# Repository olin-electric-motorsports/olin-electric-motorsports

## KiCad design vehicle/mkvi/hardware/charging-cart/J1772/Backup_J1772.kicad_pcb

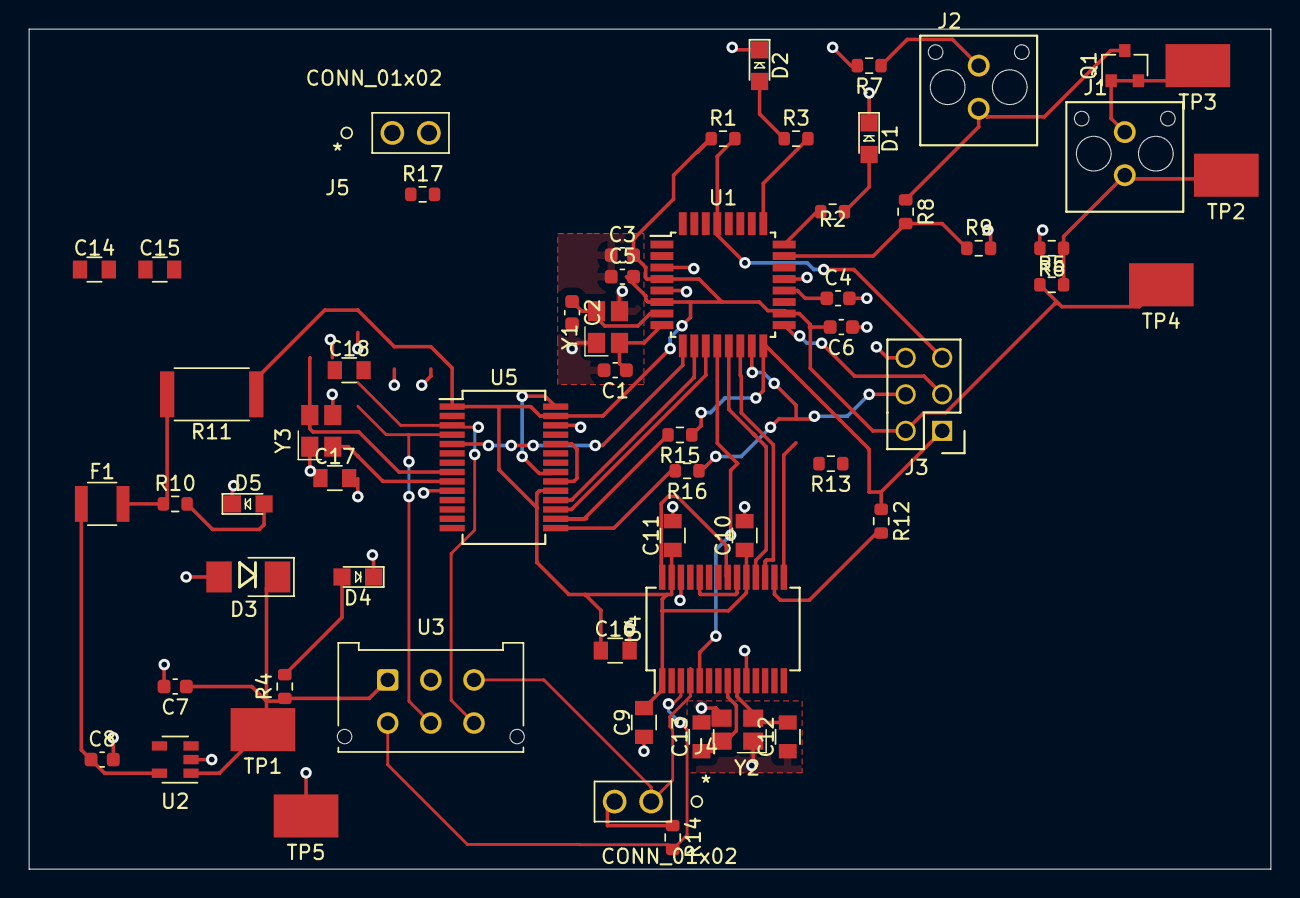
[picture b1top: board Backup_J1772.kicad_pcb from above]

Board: 2 copper layers, 86.4 x 58.4 mm, 60 parts (0 on the bottom side), 47 nets.

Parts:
C1, C2: C_30pF; C_0603_1608Metric
C3, C5, C6: C_0.1uF; C_0603_1608Metric
C4: C_100nF; C_0603_1608Metric
C7, C8: C_1uF; C_0603_1608Metric
C9, C10, C11, C14, C15, C16: C_0.1uF; C_0805_OEM
C12, C13, C17, C18: C_30pF; C_0805_OEM
D1: LED_0805_Red; LED_0805_OEM
D2, D4, D5: LED_0805; LED_0805_OEM
D3: D_Zener_18V; DO-214AA
F1: F_500mA_16V; Fuse_1210
J1, J2: MicroFit_V_2
J3: CONN_02X03; Pin_Header_Straight_2x03
J4, J5: CONN_01x02; pinheader_1x2
Q1: SSM3K333R; SOT-23F
R1: R_10K; R_0603_1608Metric
R2, R3, R4, R9: R_1K; R_0603_1608Metric
R5: R_330; R_0603_1608Metric
R6: R_2.2K; R_0603_1608Metric
R7: R_1.43K; R_0603_1608Metric
R8: R_1.91K; R_0603_1608Metric
R10: R_200; R_0603_1608Metric
R11: R_0_2512; R_2512_OEM
R12, R13, R15, R16: R_500; R_0603_1608Metric
R14, R17: R_120; R_0603_1608Metric
TP1, TP2, TP3, TP4: TP; Test_Point_SMD
TP5: Test_Point_SMD
U1: ATmega328P-AU; TQFP-32_7x7mm_P0.8mm
U2: AP7370; SOT-23-5
U3: MicroFit_VT_6
U4, U5: SSOP-28_5.3x10.2mm_P0.65mm
Y1: Crystal_SMD; Crystal_SMD_FA238
Y2, Y3: Crystal_SMD_FA238

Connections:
+5V: C3.2, C5.2, C6.2, C9.2, C10.1, C11.1, C14.2, C15.1, C16.1, J3.2, R1.1, R5.1, R11.1, TP4.1 (TP), U1.4 (VCC), U1.6 (VCC), U1.18 (AVCC), U4.1 (VIO), U4.19 (VDD), U4.27 (VDDA), U5.1 (VIO), U5.19 (VDD), U5.27 (VDDA)
+12V: C7.1, D3.1 (K), R4.1, TP1.1 (TP), U2.1 (Vin), U3.1
/CAR_CAN_+: J4.1, U3.3, U4.4 (CANH)
/CAR_CAN_-: R14.2, U3.4, U4.3 (CANL)
/CAR_CS: U1.14 ((PCINT2/~SS/OC1B)PB2), U4.17 (~CS)
/CAR_RESET: U1.13 ((PCINT1/OC1A)PB1), U4.18 (~RESET)
/CAR_STBY: U1.12 ((PCINT0/CLKO/ICP1)PB0), U4.5 (STBY)
/CHARGER_CAN_+: J5.1, U3.5, U5.4 (CANH)
/CHARGER_CAN_-: R17.2, U3.6, U5.3 (CANL)
/CHARGER_CS: U1.11 ((PCINT23/AIN1)PD7), U5.17 (~CS)
/CHARGER_RESET: U1.10 ((PCINT22/OC0A/AIN0)PD6), U5.18 (~RESET)
/CHARGER_STBY: U1.9 ((PCINT21/OC0B/T1)PD5), U5.5 (STBY)
/EVSE PWM: R8.2, R9.1, U1.23 ((ADC0/PCINT8)PC0)
/MISO: J3.1, R12.1, R15.1, U1.16 ((PCINT3/MISO)PB4)
/MOSI: J3.4, R13.1, R16.1, U1.15 ((PCINT3/OC2A/MOSI)PB3)
/RESET: J3.5, R1.2, U1.29 ((~RESET/PCINT14)PC6)
/SCK: J3.3, U1.17 ((SCK/PCINT5)PB5)
/control_pilot: J1.2, Q1.1 (G), Q1.2 (S), TP3.1 (TP)
GND: C1.2, C2.2, C3.1, C4.2, C5.1, C6.1, C7.2, C8.2, C9.1, C10.2, C11.2, C12.1, C13.2, C14.1, C15.2, C16.2, C17.1, C18.2, D1.1 (K), D2.1 (K), D3.2 (A), D4.1 (K), D5.1 (K), J3.6, R6.2, R7.2, R9.2, TP5.1, U1.3 (GND), U1.5 (GND), U1.21 (GND), U2.2 (GND), U3.2, U4.10 (GND), U4.26 (VSS), U5.10 (GND), U5.26 (VSS), Y1.2, Y1.4, Y2.2, Y2.4, Y3.2, Y3.4
unnamed: C1.1, U1.8 ((PCINT7/XTAL2/TOSC2)PB7), Y1.1
unnamed: C2.1, U1.7 ((PCINT6/XTAL1/TOSC1)PB6), Y1.3
unnamed: C4.1, U1.20 (AREF)
unnamed: C8.1, F1.1, U2.5 (Vout)
unnamed: C12.2, U4.9 (OSC1), Y2.1
unnamed: C13.1, U4.8 (OSC2), Y2.3
unnamed: C17.2, U5.9 (OSC1), Y3.1
unnamed: C18.1, U5.8 (OSC2), Y3.3
unnamed: D1.2 (A), R2.1
unnamed: D2.2 (A), R3.1
unnamed: D4.2 (A), R4.2
unnamed: D5.2 (A), R10.2
unnamed: F1.2, R10.1, R11.2
unnamed: J1.1, R5.2, R6.1, TP2.1 (TP)
unnamed: J2.1, Q1.3 (D), R8.1
unnamed: J2.2, R7.1
unnamed: J4.2, R14.1
unnamed: J5.2, R17.1
unnamed: R2.2, U1.24 ((ADC1/PCINT9)PC1)
unnamed: R3.2, U1.25 ((ADC2/PCINT10)PC2)
unnamed: R12.2, U4.16 (SO)
unnamed: R13.2, U4.15 (SI)
unnamed: R15.2, U5.16 (SO)
unnamed: R16.2, U5.15 (SI)
unnamed: U4.20 (TxCAN), U4.24 (TXD)
unnamed: U4.21 (RxCAN), U4.28 (RXD)
unnamed: U5.20 (TxCAN), U5.24 (TXD)
unnamed: U5.21 (RxCAN), U5.28 (RXD)

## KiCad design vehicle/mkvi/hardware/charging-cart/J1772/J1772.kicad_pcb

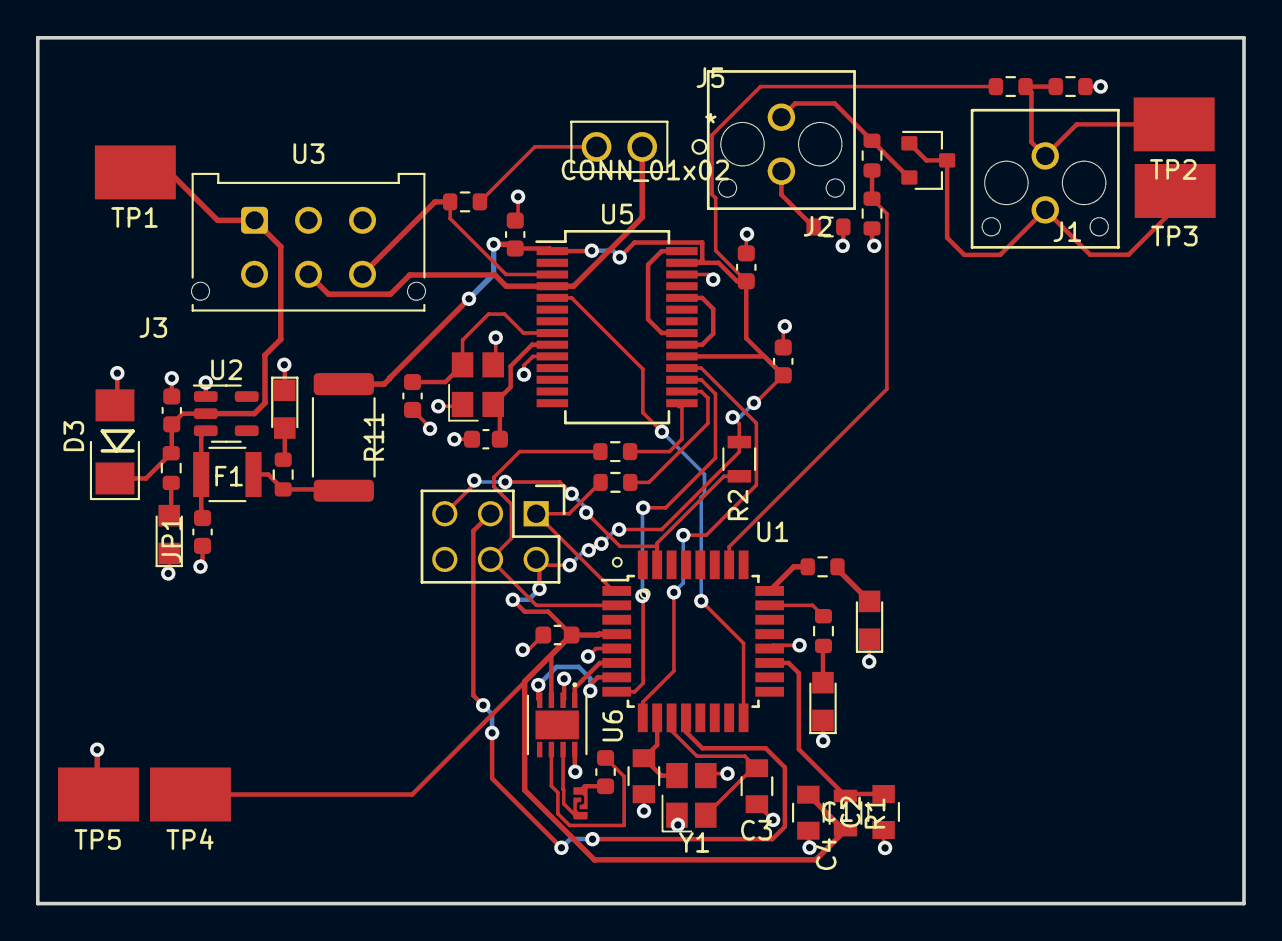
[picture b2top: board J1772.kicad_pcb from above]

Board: 2 copper layers, 67.0 x 48.1 mm, 52 parts (0 on the bottom side), 40 nets.

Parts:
C1: C_0.1uF; C_0805_OEM
C2: C_100pF; C_0805_OEM
C3, C4: C_30pF; C_0805_OEM
C5: C_0.1uF; C_0603_1608Metric
C7, C8: C_1uF; C_0603
C14, C15, C16: 0.1uF; C_0603
C17, C18: C_30pF; C_0603
D3: SMBJ5355B-TP; DO-214AA
D4, D5, D6, D7: WHITE; CHIPLED_0805
F1: F_500mA_16V; Fuse_1210
J1, J2: MicroFit_V_2
J3: CONN_02x03; Pin_Header_Straight_2x03
J5: CONN_01x02; pinheader_1x2
JP1: SolderJumper; SolderJumper-2_Open_Hooks0.8x1.8mm
Q1: SSM3K333R; SOT-23F
R1: R_100; R_0805_OEM
R2: R_10K; R_0805_OEM
R3: R_120; R_0603_1608Metric
R4, R9, R19, R20: R_1K; R_0603
R5: R_330; R_0603
R6: R_2.2K; R_0603
R7: R_1.43K; R_0603
R8: R_1.91K; R_0603
R10: 1KR; R_0603
R11: R_0_2512; R_2512_6332Metric
R15, R16: R_499; R_0603
R17: R_120; R_0603
TP1, TP2, TP3, TP4: TP; Test_Point_SMD
TP5: Test_Point_SMD
U1: ATMEGA16M1; TQFP-32_7x7mm_Pitch0.8mm
U2: TLV70450DBVR; SOT-23-5
U3: MicroFit_VT_6
U5: SSOP-28_5.3x10.2mm_P0.65mm
U6: MCP2561-E_SN; DFN8_3x3MC_MCH
Y1: Crystal_SMD; Crystal_SMD_FA238
Y3: Crystal_TXC7M

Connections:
+5V: C1.1, C5.1, C14.2, C15.1, C16.1, J3.2, R1.1, R2.1, R5.1, R11.1, TP4.1, U1.4 (VCC), U5.1 (VIO), U5.19 (VDD), U5.27 (VDDA), U6.3 (VDD)
+12V: C7.1, D3.1 (K), R4.1, TP1.1, U2.2 (VI), U3.1
/CAN_+: JP1.2 (B), U6.7 (CANH)
/CAN_-: R3.2, U6.6 (CANL)
/CAN_RX: U1.7 ((PCINT11/T1/ICP1B/RXCAN)PC3), U6.4 (RXD)
/CAN_TX: U1.6 ((PCINT10/T0/TXCAN)PC2), U6.1 (TXD)
/CHARGER_CAN_+: J5.1, U3.5, U5.4 (CANH)
/CHARGER_CAN_-: R17.2, U3.6, U5.3 (CANL)
/CHARGER_CS: U1.8 ((PCINT0/MISO/PSCOUT2A)PB0), U5.17 (~CS)
/CHARGER_RESET: U1.9 ((PCINT1/MOSI/PSCOUT2B)PB1), U5.18 (~RESET)
/CHARGER_STBY: U1.16 ((PCINT2/ADC5/INT1/ACMPN0)PB2), U5.5 (STBY)
/EVSE PWM: R8.2, R9.1, U1.26 ((PCINT5/ADC6/INT2/ACMPN1/AMP2-)PB5)
/MISO: J3.1, R15.1, U1.1 ((PCINT18/PSCIN2/OC1A/MISO_A)PD2)
/MOSI: J3.4, R16.1, U1.2 ((PCINT19/TXD/TXLIN/OC0A/~SS/MOSI_A)PD3)
/RESET: J3.5, R2.2, U1.31 ((PCINT24/OCD/~RESET)PE0)
/SCK: J3.3, U1.12 ((PCINT20/ADC1/RXD/RXLIN/ICP1A/SCK_A)PD4)
/control_pilot: J1.2, Q1.1 (G), Q1.3 (D), TP3.1
/proximity_pilot: J1.1, R5.2, R6.1, TP2.1
GND: C1.2, C2.2, C3.2, C4.2, C5.2, C7.2, C8.2, C14.1, C15.2, C16.2, C17.1, C18.2, D3.2 (A), D4.1 (K), D5.1 (K), D6.1 (K), D7.1 (K), J3.6, R6.2, R7.2, R9.2, TP5.1, U1.5 (GND), U1.20 (AGND), U2.1 (GND), U3.2, U5.10 (GND), U5.26 (VSS), U6.2 (VSS), U6.8 (STBY), Y1.2, Y1.4, Y3.2, Y3.4
unnamed: D4.2 (A), R4.2
unnamed: D5.2 (A), R10.2
unnamed: D6.2 (A), R19.2
unnamed: D7.2 (A), R20.2
unnamed: F1.2, R10.1, R11.2
unnamed: J2.2, R7.1
unnamed: J5.2, R17.1
unnamed: JP1.1 (A), R3.1
unnamed: J2.1, Q1.2 (S), R8.1
unnamed: R19.1, U1.23 ((PCINT3/AMP0-)PB3)
unnamed: R20.1, U1.24 ((PCINT4/AMP0+)PB4)
unnamed: C4.1, U1.10 ((PCINT25/OC0B/XTAL1)PE1), Y1.3
unnamed: C3.1, U1.11 ((PCINT26/ADC0/XTAL2)PE2), Y1.1
unnamed: C2.1, R1.2, U1.19 (AVCC)
unnamed: C8.1, F1.1, U2.3 (VO)
unnamed: C17.2, U5.9 (OSC1), Y3.1
unnamed: C18.1, U5.8 (OSC2), Y3.3
unnamed: U5.21 (RxCAN), U5.28 (RXD)
unnamed: R16.2, U5.15 (SI)
unnamed: R15.2, U5.16 (SO)
unnamed: U5.20 (TxCAN), U5.24 (TXD)

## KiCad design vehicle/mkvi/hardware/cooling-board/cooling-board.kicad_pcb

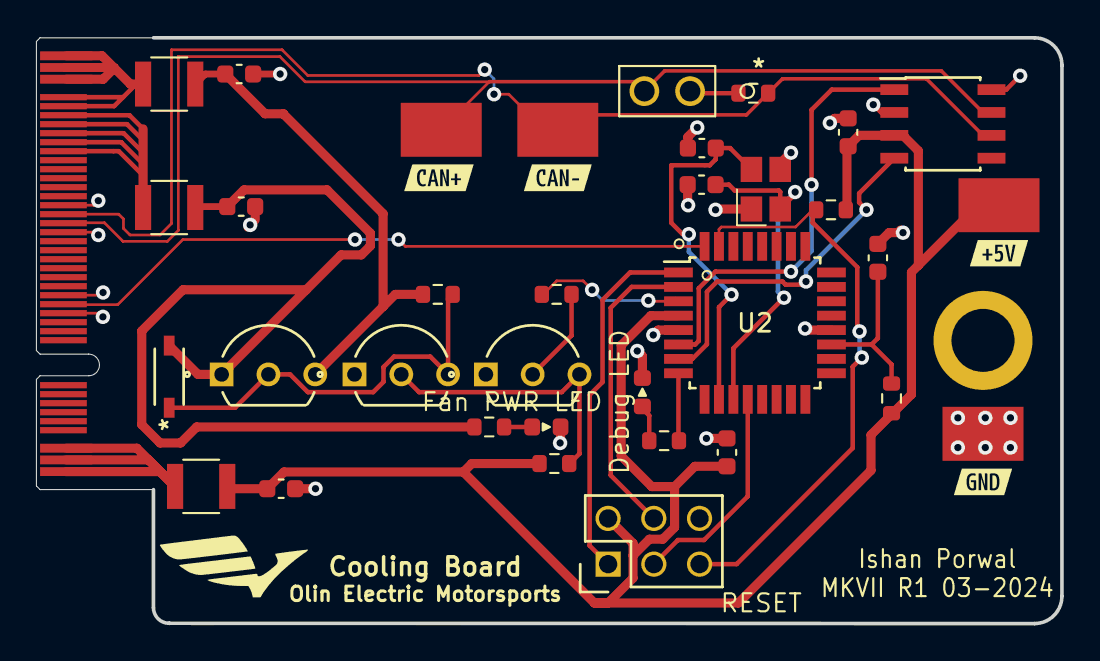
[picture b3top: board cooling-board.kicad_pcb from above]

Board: 2 copper layers, 57.0 x 32.5 mm, 40 parts (0 on the bottom side), 27 nets.

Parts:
C1, C2: C_0.1uF; C_0603
C3: C_100pF; C_0603
C4, C5: C_30pF; C_0603
C6, C7, C8: C_10uF; C_0603
CR1: 1N4148W-13-F
D1: Fan_Power_Led; LED_0603_1608Metric
D2: +5V LED; LED_0603_1608Metric
F1, F2, F3: F_500mA_16V; Fuse_1210
H1: M.2_MountingHole; M.2_Mount
J1: Automotive_M.2; Automotive_M.2_Edge_Connector
J2: CONN_02x03; Pin_Header_Straight_2x03
JP1: SolderJumper_2_Open; pinheader_1x2
R1: R_100; R_0603
R2: R_120_DNP; R_0603
R3: R_10K; R_0603
R4, R5, R6: R_4.7K; R_0603
R7: R_510; R_0603
R8: R_160; R_0603
TP1, TP2, TP3, TP4: TP_SMD; Test_Point_SMD
U1: MCP2561-E_SN; SOIC-8_3.9x4.9mm_Pitch1.27mm_OEM
U2: ATMEGA16M1; TQFP-32_7x7mm_Pitch0.8mm
U3, U4, U5: PN2222ABU
Y1: Crystal_SMD; Crystal_SMD_FA238
kibuzzard-65EFA7CF: G***; kibuzzard-65EFA7CF
kibuzzard-65EFA8D0: G***; kibuzzard-65EFA8D0
kibuzzard-65EFA79B: G***; kibuzzard-65EFA79B
kibuzzard-65EFA786: G***; kibuzzard-65EFA786

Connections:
+5V: C1.1, C2.1, C6.1, F1.1, J2.2, R1.1, R3.1, R5.2, TP1.1, U1.3 (VDD), U2.4 (VCC)
+BATT: C8.1, F3.1, R6.1, U5.3 (COLLECTOR)
/CAN_+: J1.23, JP1.2 (B), TP2.1, U1.7 (CANH)
/CAN_-: J1.24, R2.2, TP3.1, U1.6 (CANL)
/CAN_RX: U1.4 (RXD), U2.7 ((PCINT11/T1/ICP1B/RXCAN)PC3)
/CAN_TX: U1.1 (TXD), U2.6 ((PCINT10/T0/TXCAN)PC2)
/Fan Power: C7.1, CR1.2, F2.1, R7.2, U5.1 (EMITTER)
/Fan Signal: R4.1, U2.3 ((PCINT9/PSCIN1/OC1B/~SS_A)PC1)
/MISO: J2.1, U2.1 ((PCINT18/PSCIN2/OC1A/MISO_A)PD2)
/MOSI: J2.4, U2.2 ((PCINT19/TXD/TXLIN/OC0A/~SS/MOSI_A)PD3)
/RESET: J2.5, R3.2, U2.31 ((PCINT24/OCD/~RESET)PE0)
/SCK: J2.3, U2.12 ((PCINT20/ADC1/RXD/RXLIN/ICP1A/SCK_A)PD4)
/pump_PWM: J1.14, U2.32 ((PCINT17/CLKO/PSCIN0)PD1)
GND: C1.2, C2.2, C3.2, C4.2, C5.2, C6.2, C7.2, C8.2, D1.1 (K), D2.1 (K), H1.1, J1.13, J1.15, J1.22, J1.25, J2.6, TP4.1, U1.2 (VSS), U1.8 (STBY), U2.5 (GND), U2.20 (AGND), U3.1 (EMITTER), U4.1 (EMITTER), Y1.2, Y1.4
unnamed: D1.2 (A), R7.1
unnamed: D2.2 (A), R8.2
unnamed: F1.2, J1.P1, J1.P2, J1.P3
unnamed: F2.2, J1.31, J1.32, J1.33, J1.34, J1.35
unnamed: F3.2, J1.36, J1.37, J1.P38, J1.P39, J1.P40
unnamed: JP1.1 (A), R2.1
unnamed: R8.1, U2.8 ((PCINT0/MISO/PSCOUT2A)PB0)
unnamed: C4.1, U2.10 ((PCINT25/OC0B/XTAL1)PE1), Y1.3
unnamed: C5.1, U2.11 ((PCINT26/ADC0/XTAL2)PE2), Y1.1
unnamed: C3.1, R1.2, U2.19 (AVCC)
unnamed: R4.2, U3.2 (BASE)
unnamed: R5.1, U3.3 (COLLECTOR), U4.2 (BASE)
unnamed: CR1.1, R6.2, U4.3 (COLLECTOR), U5.2 (BASE)

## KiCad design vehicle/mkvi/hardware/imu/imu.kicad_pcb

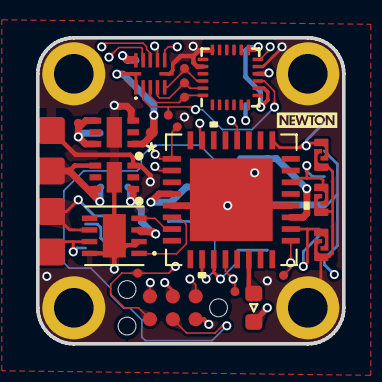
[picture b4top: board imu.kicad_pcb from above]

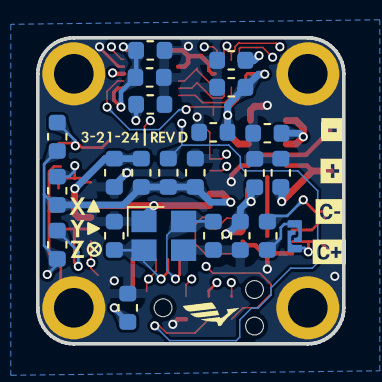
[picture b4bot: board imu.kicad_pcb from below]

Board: 4 copper layers, 17.0 x 17.0 mm, 56 parts (31 on the bottom side), 28 nets.

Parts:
C1, C2, C7, C9, C13, C14, C15: C_0.1uF; C_0603_1608Metric
C3: C_100pF; C_0603_1608Metric
C4, C5: C_30pF; C_0603_1608Metric
C6, C8, C10, C11: C_1uF; C_0603_1608Metric
D1: LED_WHITE; LED_0603_1608Metric
J1, J3, J4, J5: SMD_WIRE_TO_BOARD; SolderWirePad_1x01_SMD_1.5x1.5mm
J2: TagConnect_6; TC2030-IDC-NL
JP1, JP2, JP3, JP4: SolderJumper; SolderJumper-2_Open_Hooks0.8x1.8mm
R1: R_100; R_0603_1608Metric
R2: R_120; R_0603_1608Metric
R3: R_10K; R_0603_1608Metric
R4: R_330; R_0603_1608Metric
R5, R6, R7: R_10k; R_0603_1608Metric
TP2, TP3, TP5, TP6, TP7, TP8, TP9, TP10, TP11, TP12: TestPoint; TestPoint_Pad_D0.5mm
U1: MCP2561-E_SN; DFN8_3x3MC_MCH
U2: ATMEGA16M1; 32-QFN
U3: ICM-20948; InvenSense_QFN-24_3x3mm_P0.4mm
U4: NCP718BMT500TBG; 6-WDFN
U5: NCP705MT18TCG; 6-WDFN
U6: TXB0104RUTR
Y1: Crystal_SMD; Crystal_SMD_FA238
kibuzzard-64F4F67B: G***; kibuzzard-64F4F67B
kibuzzard-64F4F671: G***; kibuzzard-64F4F671
kibuzzard-64F4F681: G***; kibuzzard-64F4F681
kibuzzard-65FD3539: G***; kibuzzard-65FD3539
kibuzzard-647D6A7A: G***; kibuzzard-647D6A7A
kibuzzard-647D6A61: G***; kibuzzard-647D6A61
kibuzzard-647D6A73: G***; kibuzzard-647D6A73
kibuzzard-647D6F9C: G***; kibuzzard-647D6F9C

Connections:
+1V8: C7.1, C11.1, C13.2, C14.1, TP3.1, U3.8 (VDDIO), U3.13 (VDD), U5.1 (Vout), U6.1 (VCCA), U6.12 (OE)
+5V: C1.1, C2.1, C8.1, C10.1, C15.1, J2.2, R1.1, R3.1, R5.1, R6.1, R7.1, TP2.1, U1.3 (VDD), U2.4 (VCC), U4.1 (Vout), U5.4 (EN), U5.6 (Vin), U6.11 (VCCB)
+BATT: C6.1, J4.1, U4.4 (EN), U4.6 (Vin)
/BIN_ID0: JP1.1 (A), R5.2, U2.18 ((PCINT13/ADC9/ACMP3/AMP1+)PC5)
/BIN_ID1: JP4.1 (A), R7.2, U2.22 ((PCINT14/ADC10/ACMP1)PC6)
/BIN_ID2: JP3.1 (A), R6.2, U2.25 ((PCINT15/D2A/AMP2+)PC7)
/CAN_+: J1.1, JP2.2 (B), U1.7 (CANH)
/CAN_-: J3.1, R2.2, U1.6 (CANL)
/CAN_RX: U1.4 (RXD), U2.7 ((PCINT11/T1/ICP1B/RXCAN)PC3)
/CAN_TX: U1.1 (TXD), U2.6 ((PCINT10/T0/TXCAN)PC2)
/CS: TP11.1, U2.17 ((PCINT12/ADC8/ACMPN3/AMP1-)PC4), U6.7 (B4)
/CS_1V8: TP12.1, U3.22 (~CS), U6.5 (A4)
/INT: U2.28 ((PCINT7/ADC4/SCK/PSCOUT0B)PB7), U3.12 (INT1)
/MISO: J2.1, TP5.1, U2.1 ((PCINT18/PSCIN2/OC1A/MISO_A)PD2), U6.10 (B1)
/MISO_1V8: TP6.1, U3.9 (SDO/AD0), U6.2 (A1)
/MOSI: J2.4, TP7.1, U2.2 ((PCINT19/TXD/TXLIN/OC0A/~SS/MOSI_A)PD3), U6.9 (B2)
/MOSI_1V8: TP8.1, U3.24 (SDA/SDI), U6.3 (A2)
/P_LED0: D1.2 (A), U2.14 ((PCINT22/ADC3/INT0/ACMPN2)PD6)
/RESET: J2.5, R3.2, U2.31 ((PCINT24/OCD/~RESET)PE0)
/SCK: J2.3, TP9.1, U2.12 ((PCINT20/ADC1/RXD/RXLIN/ICP1A/SCK_A)PD4), U6.8 (B3)
/SCK_1V8: TP10.1, U3.23 (SCL/SCLK), U6.4 (A3)
GND: C1.2, C2.2, C3.2, C4.2, C5.2, C6.2, C7.2, C8.2, C9.1, C10.2, C11.2, C13.1, C14.2, C15.2, J2.6, J5.1, JP1.2 (B), JP3.2 (B), JP4.2 (B), R4.2, U1.2 (VSS), U1.8 (STBY), U2.5 (GND), U2.20 (AGND), U2.33, U3.11 (FSYNC), U3.18 (GND), U3.20 (GND), U4.3 (GND), U5.3 (GND), U6.6 (GND), Y1.2, Y1.4
unnamed: D1.1 (K), R4.1
unnamed: JP2.1 (A), R2.1
unnamed: C5.1, U2.10 ((PCINT25/OC0B/XTAL1)PE1), Y1.3
unnamed: C4.1, U2.11 ((PCINT26/ADC0/XTAL2)PE2), Y1.1
unnamed: C3.1, R1.2, U2.19 (AVCC)
unnamed: C9.2, U3.10 (REGOUT)

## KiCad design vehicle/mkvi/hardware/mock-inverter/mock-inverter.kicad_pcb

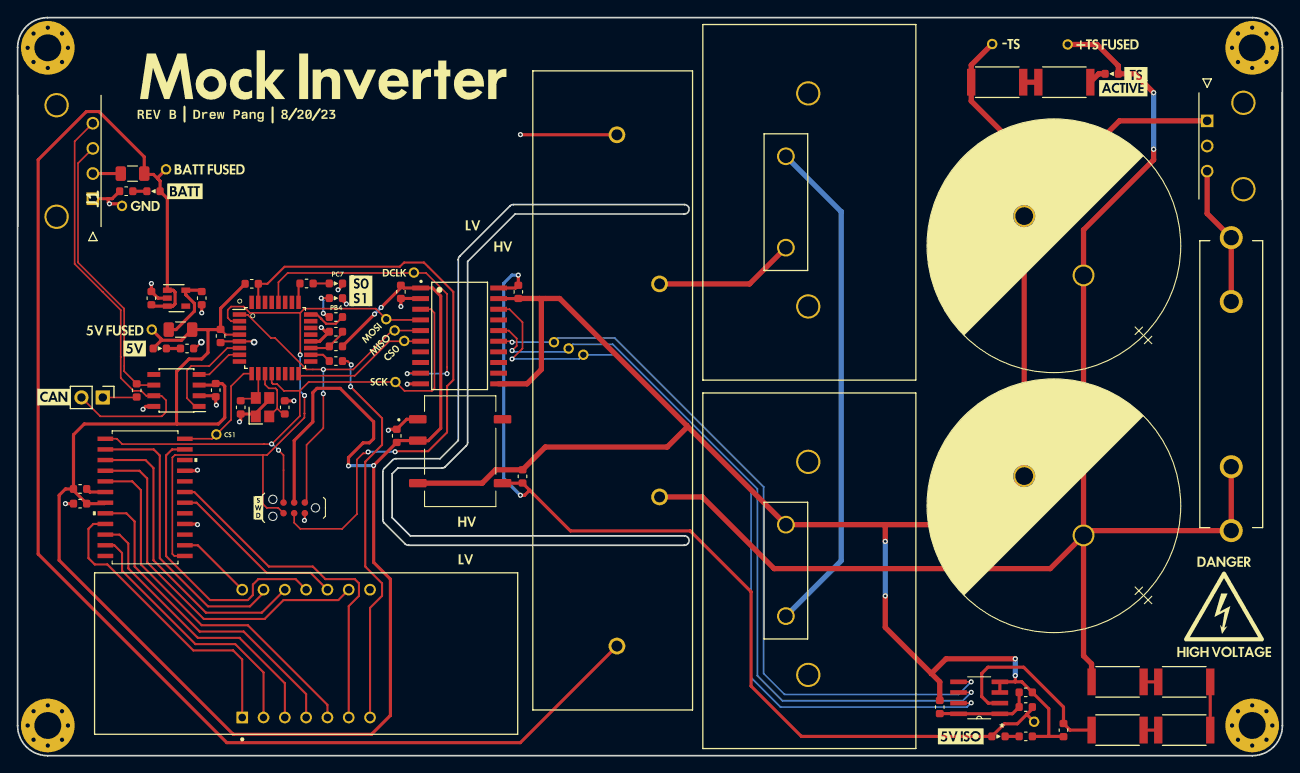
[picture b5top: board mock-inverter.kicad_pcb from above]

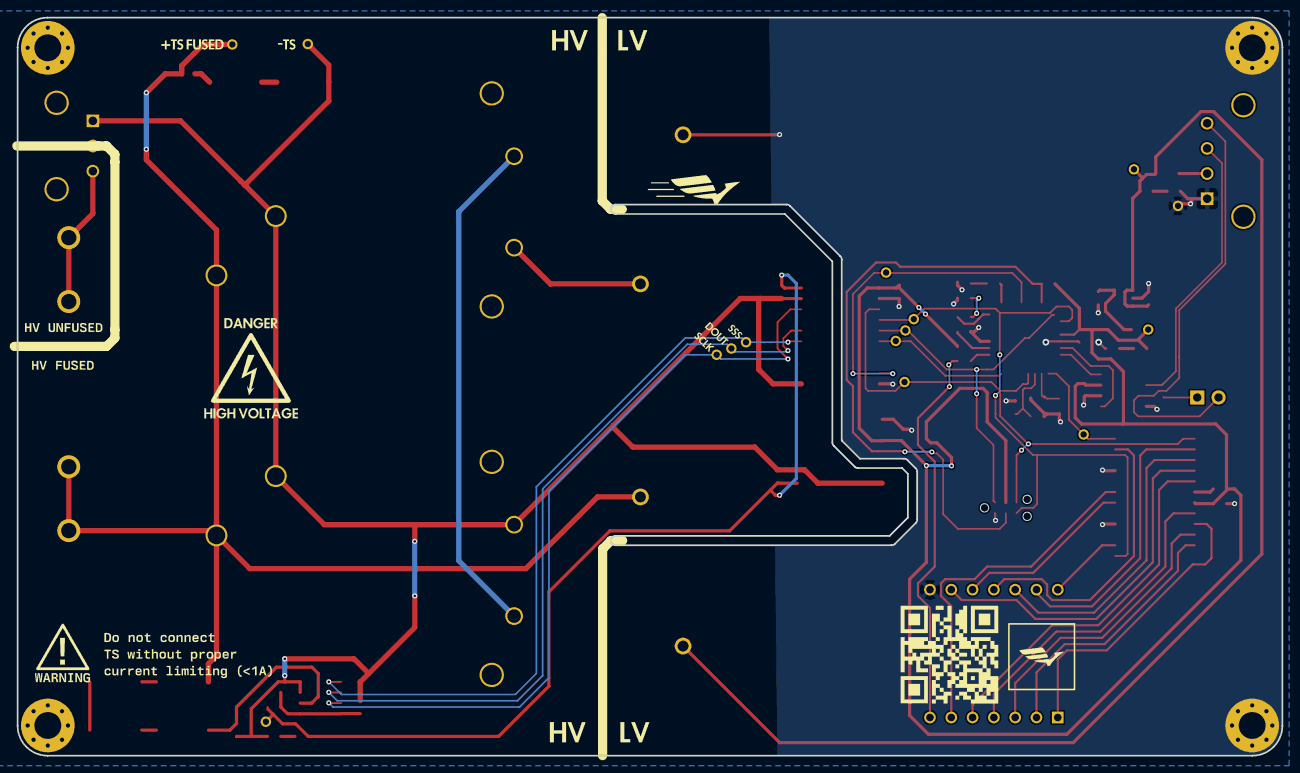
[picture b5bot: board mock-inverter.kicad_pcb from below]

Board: 2 copper layers, 150.8 x 88.0 mm, 114 parts (16 on the bottom side), 58 nets.

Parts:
C1, C3, C8, C9, C12, C13, C16: C_0.1uF; C_0603_1608Metric
C2: C_100pF; C_0603_1608Metric
C4: C_1uF; C_0603_1608Metric
C5, C6: C_30pF; C_0603_1608Metric
C7: C_2.2uF; C_0603_1608Metric
C10: C_4.7uF; C_0603_1608Metric
C11: C_10uF; C_0603_1608Metric
C14, C15: C_220uF; LLS2W221MELB
D1: 1001; Adafruit-1001-0-0-MFG
D2, D3, D4, D5, D6, D7: LED_WHITE; LED_0603_1608Metric
F1, F2: F_2A_63V; Fuse_1206
F3: 3AG_fuse_holder; 4245
J1: MicroFit_RA_4; MicroFit_RA_4x1
J2: TagConnect_6; TC2030-IDC-NL
J3: MicroFit_RA_3
JP1: Jumper_2_Open; PinHeader_1x02_P2.54mm_Vertical
K1: 3350-4275; Relay_Comus_3350
PS1: PQME1-S5-S5-M; CONV_PQME1-S5-S5-M
R1, R2: R_100; R_0603_1608Metric
R3: R25.4k; R_0603_1608Metric
R4: R_10K; R_0603_1608Metric
R5, R6, R16, R17, R18: R_499; R_0603_1608Metric
R7: R_120; R_0603_1608Metric
R8, R9, R10, R14, R15, R20: R20k; R_2512_OEM
R11, R19: R560; R_3k_HS_TO247
R12: R_1K; R_0603_1608Metric
R13: R10; R_0603_1608Metric
TP1, TP1#2, TP2, TP3, TP4, TP5, TP6: TestPoint; tp_1.25mm
U1: MAX7221CWG_1; MAX7221CWG
U2: ATMEGA16M1; TQFP-32_7x7mm_Pitch0.8mm
U3: TLV76780DBVR; SOT-23-5
U4: MCP2561-E_SN; SOIC-8_3.9x4.9mm_Pitch1.27mm_OEM
U5: ADUM4150ARIZ-RL; 20-SOIC
U6: ADS7816U; 8-SOIC
Y1: Crystal_SMD; Crystal_SMD_FA238
kibuzzard-64E2A8F0, kibuzzard-64E2A8F0#2: G***; kibuzzard-64E2A8F0
kibuzzard-64E2A90D, kibuzzard-64E2A90D#2: G***; kibuzzard-64E2A90D
kibuzzard-64E2A992: G***; kibuzzard-64E2A992
kibuzzard-64E2AB9F: G***; kibuzzard-64E2AB9F
kibuzzard-64E2ABF2: G***; kibuzzard-64E2ABF2
kibuzzard-64E2AC48: G***; kibuzzard-64E2AC48
kibuzzard-64E2AD69: G***; kibuzzard-64E2AD69
kibuzzard-64E2ADC5: G***; kibuzzard-64E2ADC5
kibuzzard-64E2ADE4: G***; kibuzzard-64E2ADE4
kibuzzard-64E2C5FA: G***; kibuzzard-64E2C5FA
kibuzzard-64E2C7B9: G***; kibuzzard-64E2C7B9
kibuzzard-64E2C88A, kibuzzard-64E2C88A#2: G***; kibuzzard-64E2C88A
kibuzzard-64E2C878, kibuzzard-64E2C878#2: G***; kibuzzard-64E2C878
kibuzzard-64E2CAF1: G***; kibuzzard-64E2CAF1
kibuzzard-64E2DCA5: G***; kibuzzard-64E2DCA5
kibuzzard-64E2DCCE: G***; kibuzzard-64E2DCCE
kibuzzard-64E2DD62: G***; kibuzzard-64E2DD62
kibuzzard-64E2DDD5, kibuzzard-64E2DDD5#2: G***; kibuzzard-64E2DDD5
kibuzzard-64E2DE7A, kibuzzard-64E2DE7A#2: G***; kibuzzard-64E2DE7A
kibuzzard-64E3F12E: G***; kibuzzard-64E3F12E
kibuzzard-64E3FA9B: G***; kibuzzard-64E3FA9B
kibuzzard-64E3FA91: G***; kibuzzard-64E3FA91
kibuzzard-64E3FAD0: G***; kibuzzard-64E3FAD0
kibuzzard-64E3FADD: G***; kibuzzard-64E3FADD
kibuzzard-64E3FB3A: G***; kibuzzard-64E3FB3A
kibuzzard-64E3FB7B: G***; kibuzzard-64E3FB7B
kibuzzard-64E3FB09: G***; kibuzzard-64E3FB09
kibuzzard-64E3FB9D: G***; kibuzzard-64E3FB9D
kibuzzard-64E29C0A: G***; kibuzzard-64E29C0A
kibuzzard-64E248A8: G***; kibuzzard-64E248A8
kibuzzard-64E248CF: G***; kibuzzard-64E248CF
kibuzzard-64E248D3: G***; kibuzzard-64E248D3
kibuzzard-64E454DF, kibuzzard-64E454DF#2: G***; kibuzzard-64E454DF
kibuzzard-64E4550C: G***; kibuzzard-64E4550C
kibuzzard-64E45533: G***; kibuzzard-64E45533
kibuzzard-64F5FD3D: G***; kibuzzard-64F5FD3D
kibuzzard-64F58BC0: G***; kibuzzard-64F58BC0
kibuzzard-64F58BCB: G***; kibuzzard-64F58BCB
kibuzzard-64F58F23: G***; kibuzzard-64F58F23
kibuzzard-64F596B1: G***; kibuzzard-64F596B1
kibuzzard-64F596E0: G***; kibuzzard-64F596E0

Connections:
+5V: C7.1, F1.1, U3.5 (Vout)
+5V_FUSED: C1.1, C3.1, C8.1, C9.1, C10.1, D5.2 (A), F1.2, J2.2, PS1.2 (VIN), R1.1, R3.1, R4.1, TP3.1, U1.19 (V+), U2.4 (VCC), U4.3 (VDD), U5.1 (VDD1)
+5V_ISO: C11.1, C12.1, D7.2 (A), PS1.5 (+VOUT), R13.1, TP6.1, U5.20 (VDD2)
+BATT: F2.1, J1.2
+BATT_FUSED: C4.1, D4.2 (A), F2.2, K1.1 (NO), TP1.1, U3.1 (Vin), U3.3 (EN)
+TS: F3.1, F3.2, J3.3
+TS_FUSED: C14.1, C15.1, D6.2 (A), F3.3, F3.4, K1.2 (COIL_1), R9.2, TP4.1
-TS: C11.2, C12.2, C13.2, C14.2, C15.2, C16.2, J3.1, PS1.4 (0V), R12.2, R18.1, R19.1, R20.1, TP5.1, U5.11 (GND2), U5.19 (GND2), U6.3 (IN-), U6.4 (GND)
/+TS_RELAY: K1.3 (COIL_2), R11.2
/CAN_+: J1.4, JP1.2 (B), U4.7 (CANH)
/CAN_-: J1.3, R7.2, U4.6 (CANL)
/CAN_RX: U2.7 ((PCINT11/T1/ICP1B/RXCAN)PC3), U4.4 (RXD)
/CAN_TX: U2.6 ((PCINT10/T0/TXCAN)PC2), U4.1 (TXD)
/COL_LED: R2.2, U2.18 ((PCINT13/ADC9/ACMP3/AMP1+)PC5)
/CS0: U2.16 ((PCINT2/ADC5/INT1/ACMPN0)PB2), U5.6 (MSS)
/CS1: U1.12 (*CS), U2.9 ((PCINT1/MOSI/PSCOUT2B)PB1)
/DCLK: U2.28 ((PCINT7/ADC4/SCK/PSCOUT0B)PB7), U5.9 (DCLK)
/DIG0: D1.14 (DIG1), U1.2 (DIG0)
/DIG1: D1.11 (DIG2), U1.11 (DIG1)
/DIG2: D1.10 (DIG3), U1.6 (DIG2)
/DIG3: D1.6 (DIG4), U1.7 (DIG3)
/DOUT: U5.16 (SO), U6.6 (DOUT)
/MISO: J2.1, U2.1 ((PCINT18/PSCIN2/OC1A/MISO_A)PD2), U5.5 (MI)
/MOSI: J2.4, TP1#2.1, U1.1 (DIN), U2.2 ((PCINT19/TXD/TXLIN/OC0A/~SS/MOSI_A)PD3), U5.4 (MO)
/P_LED0: R6.2, U2.25 ((PCINT15/D2A/AMP2+)PC7)
/P_LED1: R5.2, U2.24 ((PCINT4/AMP0+)PB4)
/RESET: J2.5, R4.2, U2.31 ((PCINT24/OCD/~RESET)PE0)
/SCK: J2.3, U1.13 (CLK), U2.12 ((PCINT20/ADC1/RXD/RXLIN/ICP1A/SCK_A)PD4), U5.3 (MCLK)
/SCLK: U5.18 (SCLK), U6.7 (DCLOCK)
/SEGA: D1.13 (A), U1.14 (SEGA)
/SEGB: D1.9 (B), U1.16 (SEGB)
/SEGC: D1.4 (C), U1.20 (SEGC)
/SEGD: D1.2 (D), U1.23 (SEGD)
/SEGDP: D1.3 (DP), U1.22 (SEGDP)
/SEGE: D1.1 (E), U1.21 (SEGE)
/SEGF: D1.12 (F), U1.15 (SEGF)
/SEGG: D1.5 (G), U1.17 (SEGG)
/SSS: U5.15 (SSS), U6.5 (*CS/SHDN)
/TS_MEAS: R12.1, R14.2, U6.2 (IN+)
GND: C1.2, C2.2, C3.2, C4.2, C5.2, C6.2, C7.2, C8.2, C9.2, C10.2, D1.8 (COL-), D2.1 (K), D3.1 (K), J1.1, J2.6, K1.4 (COM), PS1.1 (GND), R16.1, R17.1, TP2.1, U1.4 (GND), U1.9 (GND), U2.5 (GND), U2.20 (AGND), U3.2 (GND), U4.2 (VSS), U4.8 (STBY), U5.2 (GND1), U5.10 (GND1), Y1.2, Y1.4
unnamed: D1.7 (COL+), R2.1
unnamed: D2.2 (A), R5.1
unnamed: D3.2 (A), R6.1
unnamed: D4.1 (K), R16.2
unnamed: D5.1 (K), R17.2
unnamed: D6.1 (K), R10.2
unnamed: D7.1 (K), R18.2
unnamed: JP1.1 (A), R7.1
unnamed: R10.1, R20.2
unnamed: R11.1, R19.2
unnamed: R8.2, R14.1
unnamed: R8.1, R15.1
unnamed: R9.1, R15.2
unnamed: R3.2, U1.18 (ISET)
unnamed: C6.1, U2.10 ((PCINT25/OC0B/XTAL1)PE1), Y1.3
unnamed: C5.1, U2.11 ((PCINT26/ADC0/XTAL2)PE2), Y1.1
unnamed: C2.1, R1.2, U2.19 (AVCC)
unnamed: C13.1, C16.1, R13.2, U6.1 (VREF), U6.8 (VCC+)

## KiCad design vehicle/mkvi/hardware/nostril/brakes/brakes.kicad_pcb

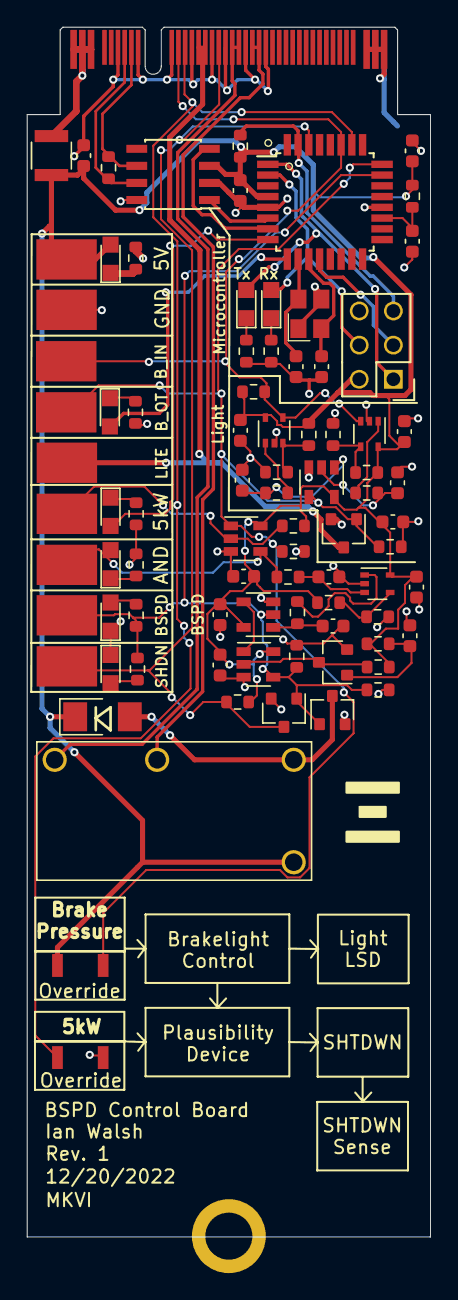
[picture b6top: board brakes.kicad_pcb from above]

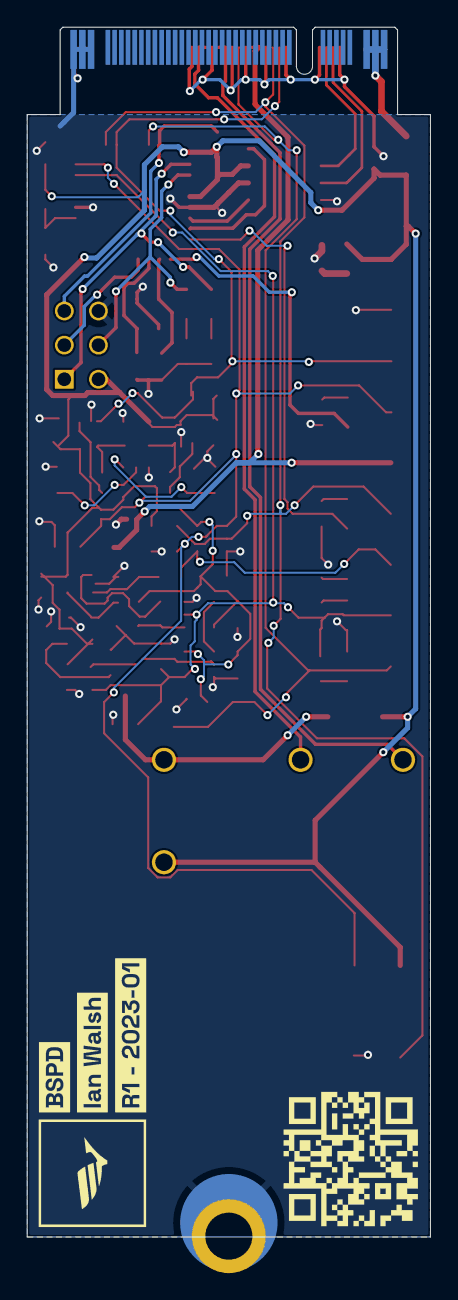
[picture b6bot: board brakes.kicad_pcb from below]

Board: 2 copper layers, 30.0 x 90.0 mm, 91 parts (4 on the bottom side), 47 nets.

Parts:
C1, C2, C5, C6, C8, C10, C11, C12, C16, C20: 0u1F; C_0603
C3, C4, C9: 1uF; C_0603
C7, C13: C_10uF; C_0603
C17: C_100pF; C_0603
C18, C19: C_30pF; C_0603
D1: BSPD_GATE_TRIP; CHIPLED_0805
D2: SMBJ5355B-TP; DO-214AA
D3: BSPD_TRIP_LED; CHIPLED_0805
D4: 5V_LED; CHIPLED_0805
D7: MOTOR ON; CHIPLED_0805
D8: BRAKES; CHIPLED_0805
D10: Shutdown_LED; CHIPLED_0805
D11: MISO_PROG_LED; CHIPLED_0805
D12: MOSI_PROG_LED; CHIPLED_0805
F1: F_500mA_16V; Fuse_1210
H1: MountingHole_Pad; M.2_Mount
J1: CONN_02x03; Pin_Header_Straight_2x03
J2: M.2_Edge; Automotive_M.2_Edge_Connector
K1: G5Q-1A4-DC5; Relay_SPST_OMRON-G5Q-1A4_OEM
Q1, Q2, Q3, Q4: SSM3K333R; SOT-23F
QR*****: hw.oem.to/6_BSPD_1; QR_6_BSPD_1
R1, R2, R6, R7, R8, R12, R13, R14, R15, R18, R25, R32: R_10K; R_0603
R3, R10, R17, R19, R26, R27, R33, R34: 1KR; R_0603
R4: R_2.2K; R_0603
R5: R_499; R_0603
R9, R16, R31, R35: 100KR; R_0603
R11: R_71.5k; R_0603
R24: R_100; R_0603
R29: R_120_DNP; R_0603
R30: 3KR; R_0603
SW1, SW2: SW_Push_SPST_NO; SW_B3U-1000P_4.2x1.7mm
TP1: B_IN; Test_Point_SMD
TP2: B_OT; Test_Point_SMD
TP3: LITE; Test_Point_SMD
TP4: AND; Test_Point_SMD
TP5: BSPD; Test_Point_SMD
TP6: 5kW; Test_Point_SMD
TP7: SHDN; Test_Point_SMD
TP8: 5V; Test_Point_SMD
TP9: GND; Test_Point_SMD
U1, U2, U5: MCP6001T-I-LT; SOT-353_SC-70-5
U3: SN74LVC1G32DBVR; SOT-23-5_OEM
U4: SN74LVC1G08DBVR; SOT-23-5_OEM
U6, U7: SN74LVC1G02DBVR; SOT-23-5_OEM
U9: ATMEGA16M1; TQFP-32_7x7mm_Pitch0.8mm
U10: MAX33011EASA; SOIC-8_3.9x4.9mm_Pitch1.27mm_OEM
Y1: Crystal_16MHz_18pF; Crystal_TXC7M
kibuzzard-63BF4696: G***; kibuzzard-63BF4696
kibuzzard-63D83579: G***; kibuzzard-63D83579
kibuzzard-63D83586: G***; kibuzzard-63D83586

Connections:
+5V: C1.1, C2.1, C5.1, C6.2, C8.2, C10.2, C12.2, C13.1, C16.1, C20.1, D2.1 (K), D4.2 (A), F1.1, J1.2, K1.5, R1.1, R2.1, R4.1, R12.1, R15.1, R16.1, R24.1, R25.1, R32.1, R35.2, SW1.1, TP8.1, U1.5 (V+), U2.5 (V+), U3.5 (VCC), U4.5 (VCC), U5.5 (V+), U6.5 (VCC), U7.5 (VCC), U9.4 (VCC), U10.3 (VDD)
/BSPD/BRAKELIGHT_LL: Q1.1 (G), R8.1, R9.2, SW1.2, TP2.1, U3.4 (out), U4.1 (in), U9.24 ((PCINT4/AMP0+)PB4)
/BSPD/BSPD_LL: Q2.1 (G), Q4.1 (G), R17.1, R18.1, R30.1, R31.1, TP5.1, U6.2 (in), U7.4 (out), U9.23 ((PCINT3/AMP0-)PB3)
/BSPD/BSPD_RELAY_IN: J2.19, J2.20, K1.3
/BSPD/BSPD_RELAY_OUT: J2.22, J2.23, K1.2
/BSPD/MOTOR_CURRENT_SENSE: J2.12, R35.1, SW2.2, TP6.1, U4.2 (in), U9.26 ((PCINT5/ADC6/INT2/ACMPN1/AMP2-)PB5)
/BrakeLight/BRAKE_PRESS_SENSE: J2.11, R1.2, TP1.1, U1.4 (-), U2.3 (+), U9.27 ((PCINT6/ADC7/PSCOUT1B)PB6)
/BrakeLight/BREAKLIGHT_CONN: J2.14, J2.15, Q1.3 (D), TP3.1
/M.2 Connector/BSPD_SHUTDOWN_SENSE: J2.17, Q4.3 (D), R32.2, TP7.1, U9.30 ((PCINT8/INT3/PSCOUT1A)PC0)
/M.2 Connector/CAN_+: J2.7, R29.1, U10.7 (CANH)
/M.2 Connector/CAN_-: J2.8, R29.2, U10.6 (CANL)
/Microcontroller - ATMEGA16M1/5KW_LED: D7.2 (A), U9.8 ((PCINT0/MISO/PSCOUT2A)PB0)
/Microcontroller - ATMEGA16M1/BRAKE_LL_LED: D8.2 (A), U9.9 ((PCINT1/MOSI/PSCOUT2B)PB1)
/Microcontroller - ATMEGA16M1/CAN_RX: U9.7 ((PCINT11/T1/ICP1B/RXCAN)PC3), U10.4 (RXD)
/Microcontroller - ATMEGA16M1/CAN_TX: U9.6 ((PCINT10/T0/TXCAN)PC2), U10.1 (TXD)
/Microcontroller - ATMEGA16M1/MISO: D11.2 (A), J1.1, U9.1 ((PCINT18/PSCIN2/OC1A/MISO_A)PD2)
/Microcontroller - ATMEGA16M1/MOSI: D12.2 (A), J1.4, U9.2 ((PCINT19/TXD/TXLIN/OC0A/~SS/MOSI_A)PD3)
/Microcontroller - ATMEGA16M1/RESET: J1.5, R25.2, U9.31 ((PCINT24/OCD/~RESET)PE0)
/Microcontroller - ATMEGA16M1/SCK: J1.3, U9.12 ((PCINT20/ADC1/RXD/RXLIN/ICP1A/SCK_A)PD4)
GND: C1.2, C2.2, C3.1, C4.1, C5.2, C6.1, C7.1, C8.1, C9.2, C10.1, C11.1, C12.1, C13.2, C16.2, C17.2, C18.2, C19.2, C20.2, D3.1 (K), D10.1 (K), H1.1, J1.6, J2.6, J2.9, J2.10, J2.13, J2.16, J2.18, J2.21, J2.24, J2.P38, J2.P39, J2.P40, Q1.2 (S), Q2.2 (S), Q3.2 (S), Q4.2 (S), R3.2, R5.2, R8.2, R9.1, R10.1, R13.2, R18.2, R19.2, R26.2, R27.2, R31.2, R33.2, R34.2, SW2.1, TP9.1, U1.2 (V-), U2.2 (V-), U3.3 (GND), U4.3 (GND), U5.2 (V-), U6.3 (GND), U7.3 (GND), U9.5 (GND), U9.20 (AGND), U10.2 (VSS), U10.8 (STBY), Y1.2, Y1.4
unnamed: C3.2, R6.2, U3.1 (in)
unnamed: C4.2, R7.2, U3.2 (in)
unnamed: C7.2, R11.2, U5.3 (+)
unnamed: C9.1, R14.2, U6.1 (in)
unnamed: C11.2, Q3.1 (G), R15.2
unnamed: C17.1, R24.2, U9.19 (AVCC)
unnamed: C18.1, U9.11 ((PCINT26/ADC0/XTAL2)PE2), Y1.1
unnamed: C19.1, U9.10 ((PCINT25/OC0B/XTAL1)PE1), Y1.3
unnamed: D1.1 (K), R10.2
unnamed: D1.2 (A), R11.1, TP4.1, U4.4 (out)
unnamed: D2.2 (A), K1.1, Q2.3 (D)
unnamed: D3.2 (A), R17.2
unnamed: D4.1 (K), R19.1
unnamed: D7.1 (K), R26.1
unnamed: D8.1 (K), R27.1
unnamed: D10.2 (A), R30.2
unnamed: D11.1 (K), R33.1
unnamed: D12.1 (K), R34.1
unnamed: F1.2, J2.P1, J2.P2, J2.P3
unnamed: Q3.3 (D), R16.2, U7.2 (in)
unnamed: R2.2, R3.1, U1.3 (+)
unnamed: R4.2, R5.1, U2.4 (-)
unnamed: R6.1, U1.1
unnamed: R7.1, U2.1
unnamed: R12.2, R13.1, U5.4 (-)
unnamed: R14.1, U5.1
unnamed: U6.4 (out), U7.1 (in)

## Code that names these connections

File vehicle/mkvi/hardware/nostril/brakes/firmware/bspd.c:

#include "bspd.h"

#include "libs/adc/api.h"
#include "libs/gpio/api.h"
#include "libs/timer/api.h"
#include "vehicle/mkv/software/bspd/can_api.h"

#include <avr/interrupt.h>

#include <stdbool.h>
#include <stdint.h>

#include "projects/btldr/btldr_lib.h"
#include "projects/btldr/git_sha.h"
#include "projects/btldr/libs/image/api.h"


//Required for btldr
image_hdr_t image_hdr __attribute__((section(".image_hdr"))) = {
    .image_magic = IMAGE_MAGIC,
    .git_sha = STABLE_GIT_COMMIT,
};

//CAN interrupt + callback function
volatile bool send_can = false;
void timer0_callback(void) {
    send_can = true;
}

volatile uint16_t brake_pressure = 0;


void pcint1_callback(void) {

    //Update CAN struct with new board logic values
    bspd.brake_gate = !!gpio_get_pin(BRAKELIGHT_LL);
    bspd.bspd_5kw = !!gpio_get_pin(MOTOR_CURRENT_SENSE);
    bspd.ss_bspd = !gpio_get_pin(BSPD_LL);

    //Update Brake Light LED on the PCB
    if (bspd.brake_gate) {
        gpio_set_pin(BRAKE_LL_LED);
    } else {
        gpio_clear_pin(BRAKE_LL_LED);
    }

    //Update 5kW LED on the PCB
    if (bspd.bspd_5kw) {
        gpio_set_pin(MOTOR_5KW_LED);
    } else {
        gpio_clear_pin(MOTOR_5KW_LED);
    }

    //Update Shutdown LED on the PCB
    if (bspd.ss_bspd) {
        gpio_set_pin(BSPD_TRIP_LED);
    } else {
        gpio_clear_pin(BSPD_TRIP_LED);
    }
}

int main(void) {
    //Not sure what this does
    sei();

    //Auto-generated
    can_init_bspd();

    //Set up the internal ADC on the Arduino - configure it to read analog brake pressure values
    adc_init();

    //Begin bootloader update function
    updater_init(BTLDR_ID, 5);

    //Start 100Hz CAN update timer
    timer_init(&timer0_cfg);

    //Connect Digital output pins to high-current IO logic
    gpio_set_mode(MOTOR_5KW_LED, OUTPUT);
    gpio_set_mode(BRAKE_LL_LED, OUTPUT);
    gpio_set_mode(BSPD_TRIP_LED, OUTPUT);

    //Enable digital inputs
    gpio_set_mode(MOTOR_CURRENT_SENSE, INPUT);
    gpio_set_mode(BSPD_LL, INPUT);

    //Attach Pins to interrupt handler (assuming on rising/falling edge)
    gpio_enable_interrupt(BRAKELIGHT_LL);
    gpio_enable_interrupt(MOTOR_CURRENT_SENSE);
    gpio_enable_interrupt(BSPD_LL);

    pcint1_callback();

    for (;;) {
        updater_loop();

        if (send_can) {
            bspd.brake_pressure = adc_read(BRAKE_PRESSURE_SENSE);
            can_send_bspd();
            send_can = false;
        }
    }
}

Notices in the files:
parts and their libraries:
Copyright 2021 Accelerated Designs. All rights reserved.
